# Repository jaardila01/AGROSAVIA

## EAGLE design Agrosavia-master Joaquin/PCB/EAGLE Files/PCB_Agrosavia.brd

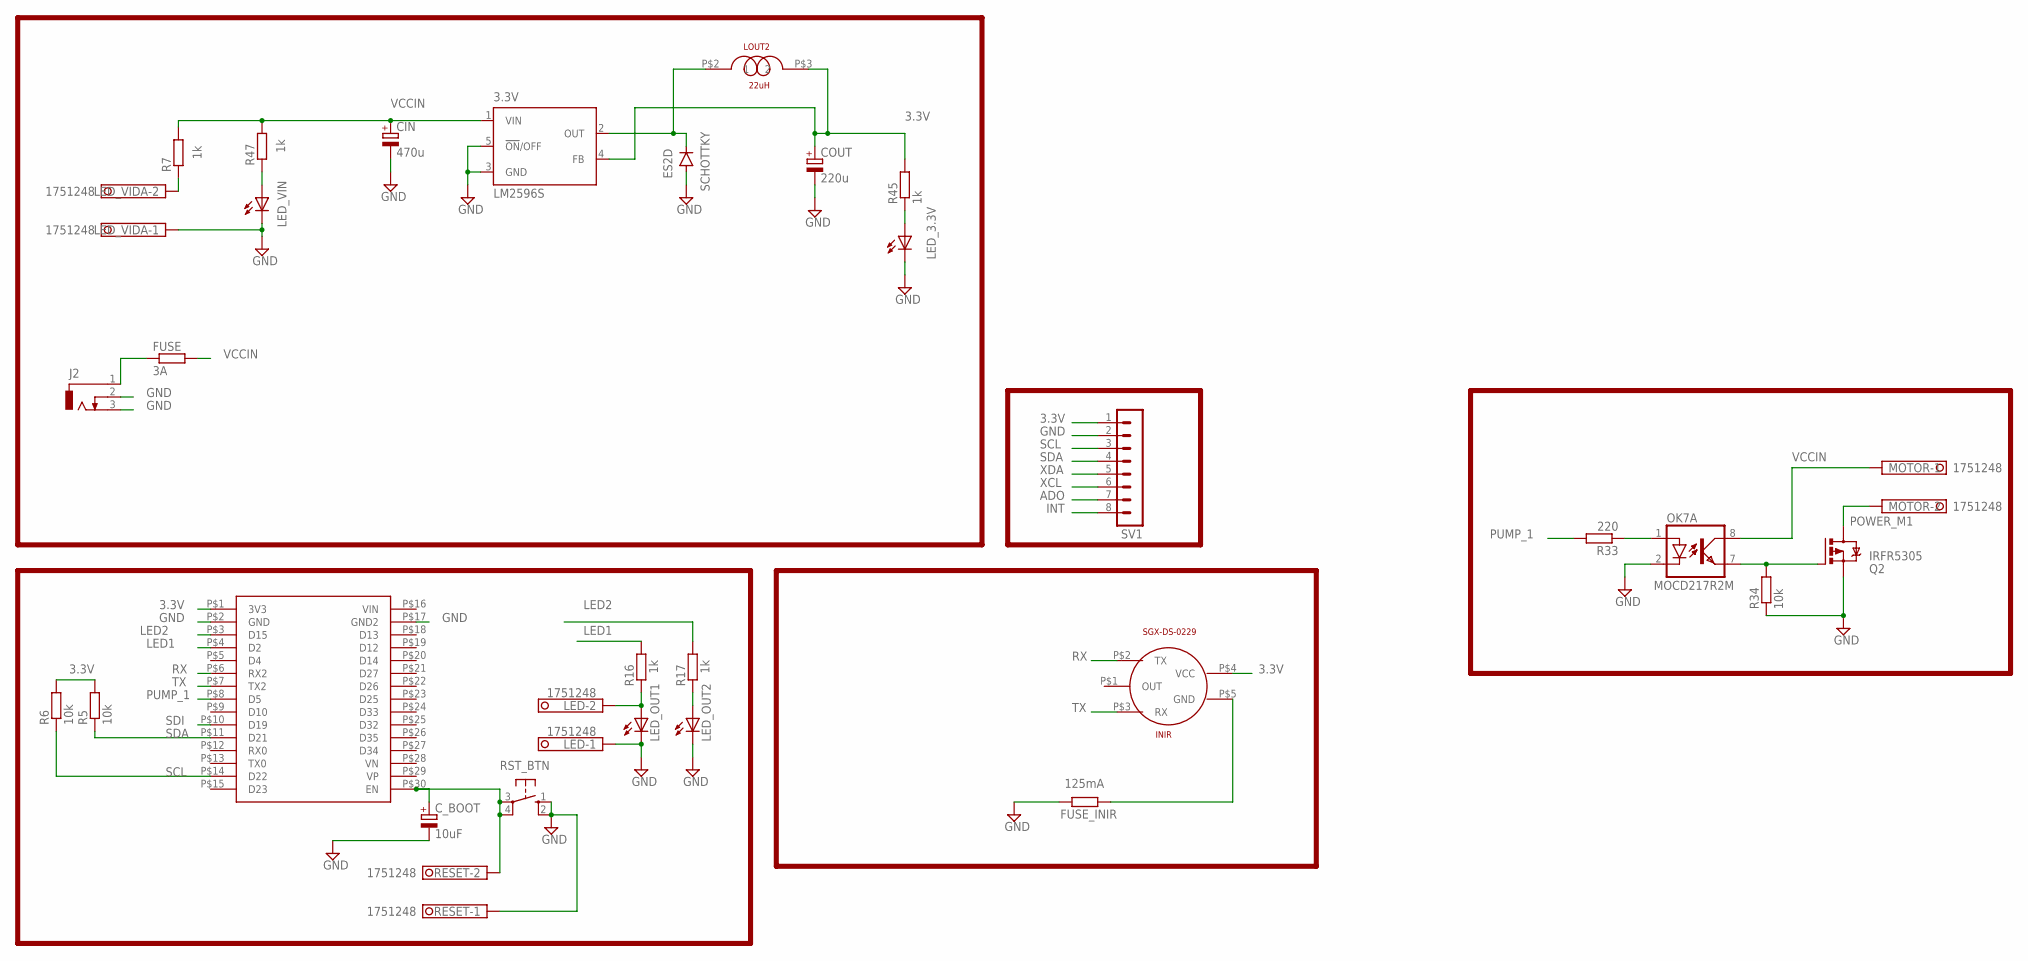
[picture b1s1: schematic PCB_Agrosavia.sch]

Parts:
3.3V: LM2596S; TO263-5
CIN: 470u; SANYO-OSCON_SMD_F12
COUT: 220u; UD-10X10_NICHICON
C_BOOT: 10uF; SANYO-OSCON_SMD_B6
ESP32DEVKITV1: ESP32
FUSE: 3A; R1206
FUSE_INIR: 125mA; R0402
J2: DCJ0303
LED: 1751248
LED_3.3V: LED_E; LED_1206
LED_OUT1, LED_OUT2: LED_E; LED_1206
LED_VIDA: 1751248
LED_VIN: LED_E; LED_1206
LOUT2: 22uH; SRP1038A
MOTOR: 1751248
OK7: MOCD217R2M; SOIC08
Q2: IRFR5305; D-PAK_TO252AA
R5, R6, R34: 10k; R1206
R7, R16, R17, R45, R47: 1k; R0805
R33: 220; R0603
RESET: 1751248
RST_BTN: 10-XX; B3F-10XX
SCHOTTKY: ES2D; SMB
SGX-DS-0229: INIR
SV1: MA08-1

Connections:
3.3V: 3.3V.4 (FB), COUT.+, ESP32DEVKITV1.P$1 (3V3), LOUT2.P$3 (2), R5.2, R6.2, R45.2, SGX-DS-0229.P$4 (VCC), SV1.1
ADO: SV1.7
GND: 3.3V.3 (GND), 3.3V.5 (!ON!/OFF), CIN.-, COUT.-, C_BOOT.-, ESP32DEVKITV1.P$2 (GND), ESP32DEVKITV1.P$17 (GND2), FUSE_INIR.2, J2.2, J2.3, LED.1, LED_3.3V.C, LED_OUT1.C, LED_OUT2.C, LED_VIDA.1, LED_VIN.C, OK7.2 (C), Q2.3 (S), R34.1, RESET.1, RST_BTN.1 (S), RST_BTN.2 (S1), SCHOTTKY.A, SV1.2
INT: SV1.8
LED1: ESP32DEVKITV1.P$4 (D2), R16.2
LED2: ESP32DEVKITV1.P$3 (D15), R17.2
unnamed: FUSE_INIR.1, SGX-DS-0229.P$5 (GND)
unnamed: C_BOOT.+, ESP32DEVKITV1.P$30 (EN), RESET.2, RST_BTN.3, RST_BTN.4 (P1)
unnamed: LED_VIDA.2, R7.1
unnamed: LED.2, LED_OUT1.A, R16.1
unnamed: LED_OUT2.A, R17.1
unnamed: OK7.1 (A), R33.1
unnamed: OK7.7 (EMIT), Q2.1 (G), R34.2
unnamed: 3.3V.2 (OUT), LOUT2.P$2 (1), SCHOTTKY.C
unnamed: LED_3.3V.A, R45.1
unnamed: LED_VIN.A, R47.1
unnamed: FUSE.1, J2.1
POWER_M1: MOTOR.2, Q2.4 (D)
PUMP_1: ESP32DEVKITV1.P$8 (D5), R33.2
RX: ESP32DEVKITV1.P$6 (RX2), SGX-DS-0229.P$2 (TX)
SCL: ESP32DEVKITV1.P$14 (D22), R6.1, SV1.3
SDA: ESP32DEVKITV1.P$11 (D21), R5.1, SV1.4
SDI: ESP32DEVKITV1.P$10 (D19)
TX: ESP32DEVKITV1.P$7 (TX2), SGX-DS-0229.P$3 (RX)
VCCIN: 3.3V.1 (VIN), CIN.+, FUSE.2, MOTOR.1, OK7.8 (COL), R7.2, R47.2
XCL: SV1.6
XDA: SV1.5

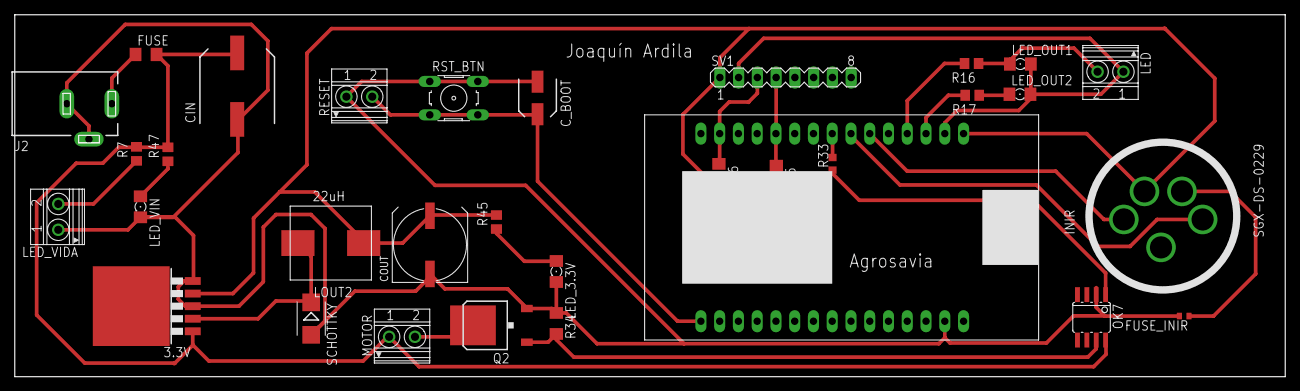
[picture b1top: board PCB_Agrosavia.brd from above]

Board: 2 copper layers, 172.0 x 49.0 mm, 32 parts (1 on the bottom side), 22 nets.

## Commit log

2021-06-17 Proyecto Agrosavia
    Repositorio para proyecto de grado Joaquín Ardila
